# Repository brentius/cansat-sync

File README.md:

# CANSAT

Local working folder for the CANSAT project, organised using ATLAS as the reference.

The current mission uses a Raspberry Pi Zero 2 W and STM32F405 to combine primary temperature/pressure telemetry with terrain-relative navigation during passive parachute descent and image-derived wind profiling. The selected hardware is defined by the [flight computer BOM](wiki/flight_computer_bom.md) and summarised in the [current design baseline](wiki/design_baseline.md).

The [all-board BOM summary](wiki/board_bom_summary.md) allocates the selected POWER, MAIN and RF boards, plus Pi, camera and shared offboard purchases. POWER contains supply electronics; MAIN contains the MCU, sensors and interfaces. The previous KiCad projects were cleared on 29 October 2026 to restart PCB design; the BOM and design notes remain reference material, and descriptions of the previous CAD are historical.

## File structure

```text
cansat/
├── pcb/                   Schematics, PCB layouts and parts libraries
├── code/                  Onboard software, ground software and data processing
├── cad/                   Mechanical designs and assembly models
├── sim/                   Simulations, analysis scripts and results
├── wiki/                  Mission proposals, documentation and reference notes
├── BOTS/
│   ├── AGENTS/            Local agent instructions
│   └── PLANS/             Architecture, plans, decisions and project status
├── README.md
├── LICENSE-HARDWARE
├── LICENSE-SOFTWARE
└── .gitignore
```

## Onboard software

The [flight software implementation report](wiki/flight_software.md) describes the
STM32 firmware, Pi service/navigation, design choices, verification and hardware
next steps. Sources are in `code/firmware/stm32`, `code/cansat`, `code/piapp` and
`code/deploy/pi`. Reproduce the combined host/cross-build gate with
`.venv/Scripts/python.exe code/tools/verify_flight.py`.

## Mission documentation

The [mission proposal](wiki/trn_secondary_mission_proposal.md) was rewritten on 13 October 2026 around the current BOM, reference interfaces and newer feasibility studies. It includes both mission software paths and distinguishes selected hardware, candidate code, targets and verified evidence. The [27 September proposal](wiki/history/trn_secondary_mission_proposal_2026-09-27.md) is retained as a historical source snapshot; it is not the current design. The original ChatGPT project source remains separate.

The standalone [mathematical derivations and verification document](wiki/cansat_mathematics.tex) covers the proposal's mathematics index, corrected assumptions, worked examples and synthetic experiments. It needs no external source files to compile and compiled successfully with the built-in editor on 13 October 2026. Its historical example inputs are preserved alongside current BOM context. The supplied 52-page PDF remains a separate historical attachment that has been audited.

The [simulation and feasibility audit](wiki/mathematics_simulation_audit.md) maps all 249 numbered PDF equations to checks and restrictions, with 76 tests reported passing in the retained audit, rendered-image experiments, navigation and atmospheric uncertainty ensembles, and processing budgets. It records a transfer-function typo and a corrected NCC memory problem. Numerical consistency is established under the tested assumptions; flight performance and current Pi Zero 2 W throughput remain unverified. Historical H618/OV9281 sizing is explicitly separated from the current baseline. Supporting code and retained results are in `sim/maths/`; project state is recorded in `BOTS/PLANS/`.

A [second review of that PDF](wiki/cansat_maths_pdf_review.md) on 13 October re-derived all 249 equations and recomputed the stated numbers: the mathematics is correct apart from one known typo and a few small slips. It also lists where the PDF's inputs and conclusions no longer match the current baseline, which of its corrections the live proposal has not yet taken up, and where the flight code departs from it. No simulation was rerun and no source was changed.

The [closed-loop navigation simulation](wiki/navigation_closed_loop_simulation.md) runs a candidate flight navigation filter (`code/cansat/eskf.py`, initialised from `code/cansat/firstfix.py` pose outputs) against a simulated parachute descent in `sim/nav/`: 109 scenarios of 160 descents each, an image-in-the-loop cross-check, a matcher-tolerance study and a canopy swing and glide study. In simulation the September proposal's plain filter loses lock under realistic errors, while the current proposal uses the hardened 17-error-state candidate, which holds about 0.6 m RMS relative to the simulated map. Canopy glide remains a major threat to wind retrieval. The acquisition-to-filter handoff is now implemented in `navigator.py`; the flight-software report covers its separate integrated evidence. All of it is synthetic: no real imagery, flight data or Pi timing yet. Inputs and their sources are in [navigation parameter sources](wiki/navigation_parameter_sources.md).

The [fine landmark tracking implementation and study](wiki/fine_landmark_tracking.md) adds the missing local image matcher in `code/cansat/fine.py`: prepared map templates, predicted-pose rectification, bounded spatial selection, ambiguity rejection and original-pixel measurements for the existing filter. `sim/nav/run_fine_mc.py` tests repeated image-to-filter corrections on procedural farmland with paired no-image controls and appearance/capture-limit stress cases. It is candidate software with synthetic verification; live acquisition/tracking orchestration is now implemented; real-image/Pi validation remains open.

The [end-to-end wind and landing study](wiki/wind_retrieval_end_to_end.md) carries that filter's output through to the mission's science products: a wind retrieval (`code/cansat/windprofile.py`) and a candidate landing predictor for the Pi Zero 2 W (`code/cansat/landing.py`), scored in `sim/nav/run_wind_mc.py` over five canopy behaviours. In simulation the simple drag-model retrieval meets its 0.5 m/s absolute-error target under a stable canopy and one with a 5 degree trim, and fails with a 12 or 25 degree trim or heavy swing, while the S1 comparison of image and GPS winds passes in every case. The current proposal therefore defines S1 as method agreement and treats absolute wind recovery and lateral-force correction as calibration-dependent. One descent's winds between 80 m and 300 m do not determine roughness length without the ground anemometer. All of it is synthetic and nothing has run on the flight hardware. Literature inputs and their evidence quality are in [wind science parameter sources](wiki/wind_science_parameter_sources.md).

The [first-fix study](wiki/acquisition_first_fix.md) covers the step before that filter can start: finding where the can is, and which way it faces, from one image with the heading unknown. `code/cansat/coarse.py` is flight code for the Pi Zero 2 W that does it in four stages and refuses instead of guessing; `sim/nav/run_acquisition_mc.py` scores it on procedural farmland (`sim/nav/farmland.py`) with rendered images and simulated descents. In simulation it gives a fix from about nine images in ten on well-hedged terrain and about four in ten on large fields, where it is also wrong more often, so the result depends on the launch site and needs real imagery of it. An independent review found seven defects, all fixed. All of it is synthetic and nothing has run on the Pi.

The [STM32-to-Pi link protocol](wiki/stm32_pi_link_protocol.md) defines the serial link between the two processors, which did not exist before: framing, twelve messages, the time base, and how camera frames get their timestamps. `code/cansat/link.py` is the Pi's end and the reference the STM32 firmware has to match, with test vectors in `code/tests/link_vectors.json`. It was checked in closed loop against the navigation Monte Carlo (`sim/nav/run_link_mc.py`). The C firmware and Pi service now exist; host/cross-build verification is recorded in the flight-software report. Nothing has been executed on either physical processor.

The [mass, power and descent budget](wiki/mass_power_budget.md) replaces the 1 October sizing, which was for hardware the project no longer uses. For the current design it expects about 335 g against the 350 g limit with a 6 to 15 % chance of exceeding it, a wide margin on three hours of power if the Pi idles while waiting, and a design descent rate too close to the 10 m/s floor. Nothing in it has been weighed or metered. The model is `sim/systems/budget.py`.

The [PDR checklist](BOTS/PLANS/PDR_FULL_MARKS_CHECKLIST.md) maps the supplied 36-point rubric and all available requirements. Those requirements are still from 2025-26; current-season rules/dates need confirmation. Completed analysis is documented separately from open firmware, physical packaging, calibration, target compute, mass/cost and flight qualification.

## Licenses

Following ATLAS, hardware designs in `pcb/` and `cad/`, and hardware circuit netlists in `sim/`, use CERN-OHL-S-2.0; software in `code/` and simulation scripts in `sim/` use GPL-3.0-only. See `LICENSE-HARDWARE` and `LICENSE-SOFTWARE`.

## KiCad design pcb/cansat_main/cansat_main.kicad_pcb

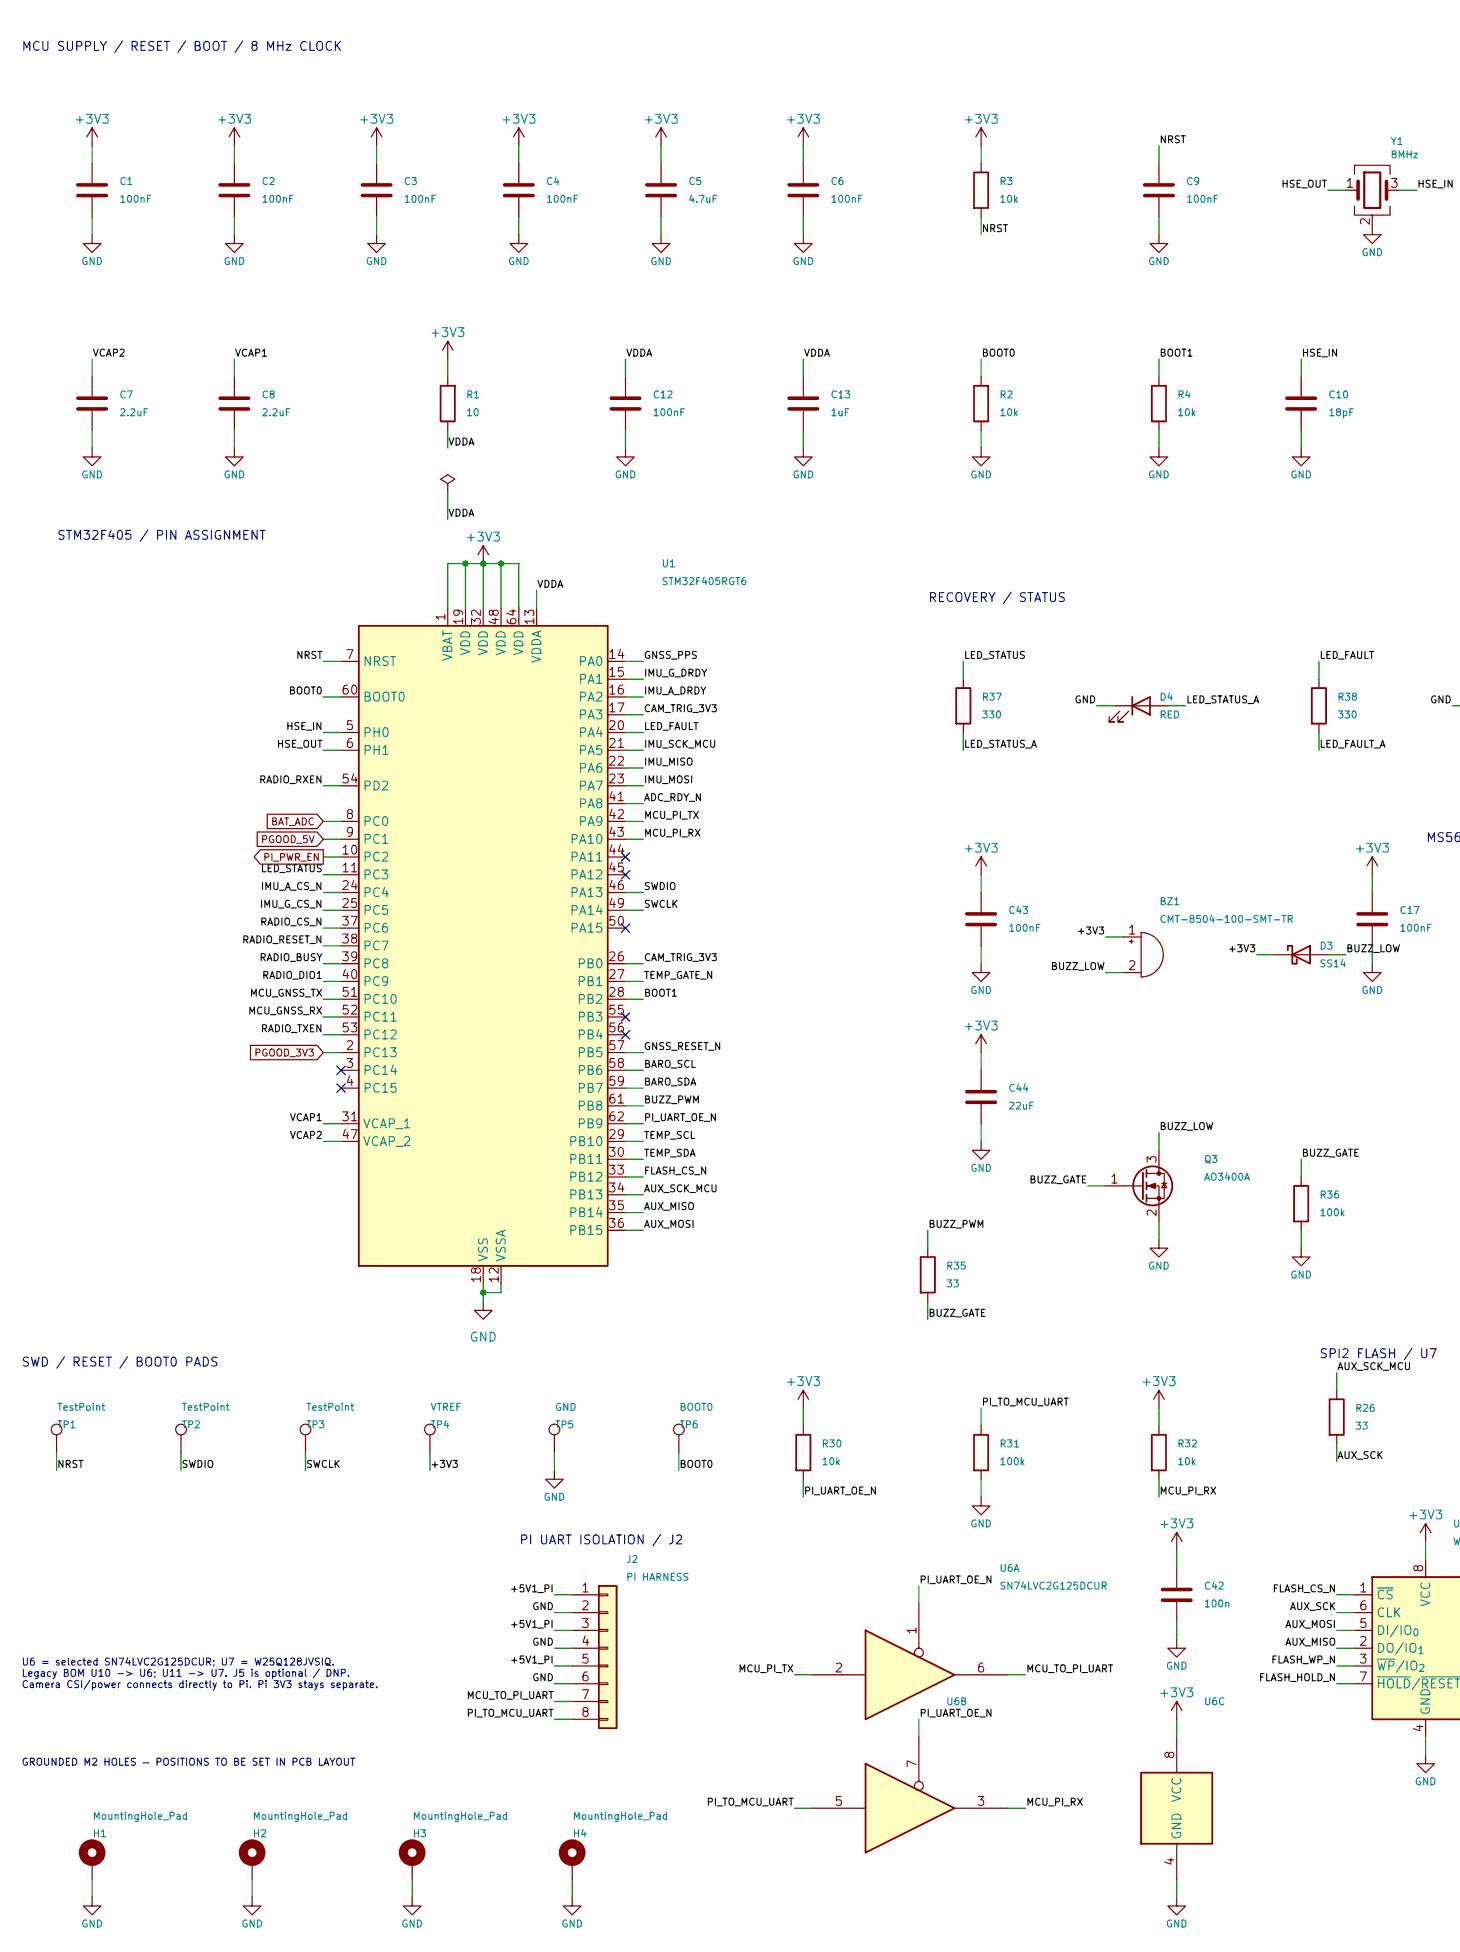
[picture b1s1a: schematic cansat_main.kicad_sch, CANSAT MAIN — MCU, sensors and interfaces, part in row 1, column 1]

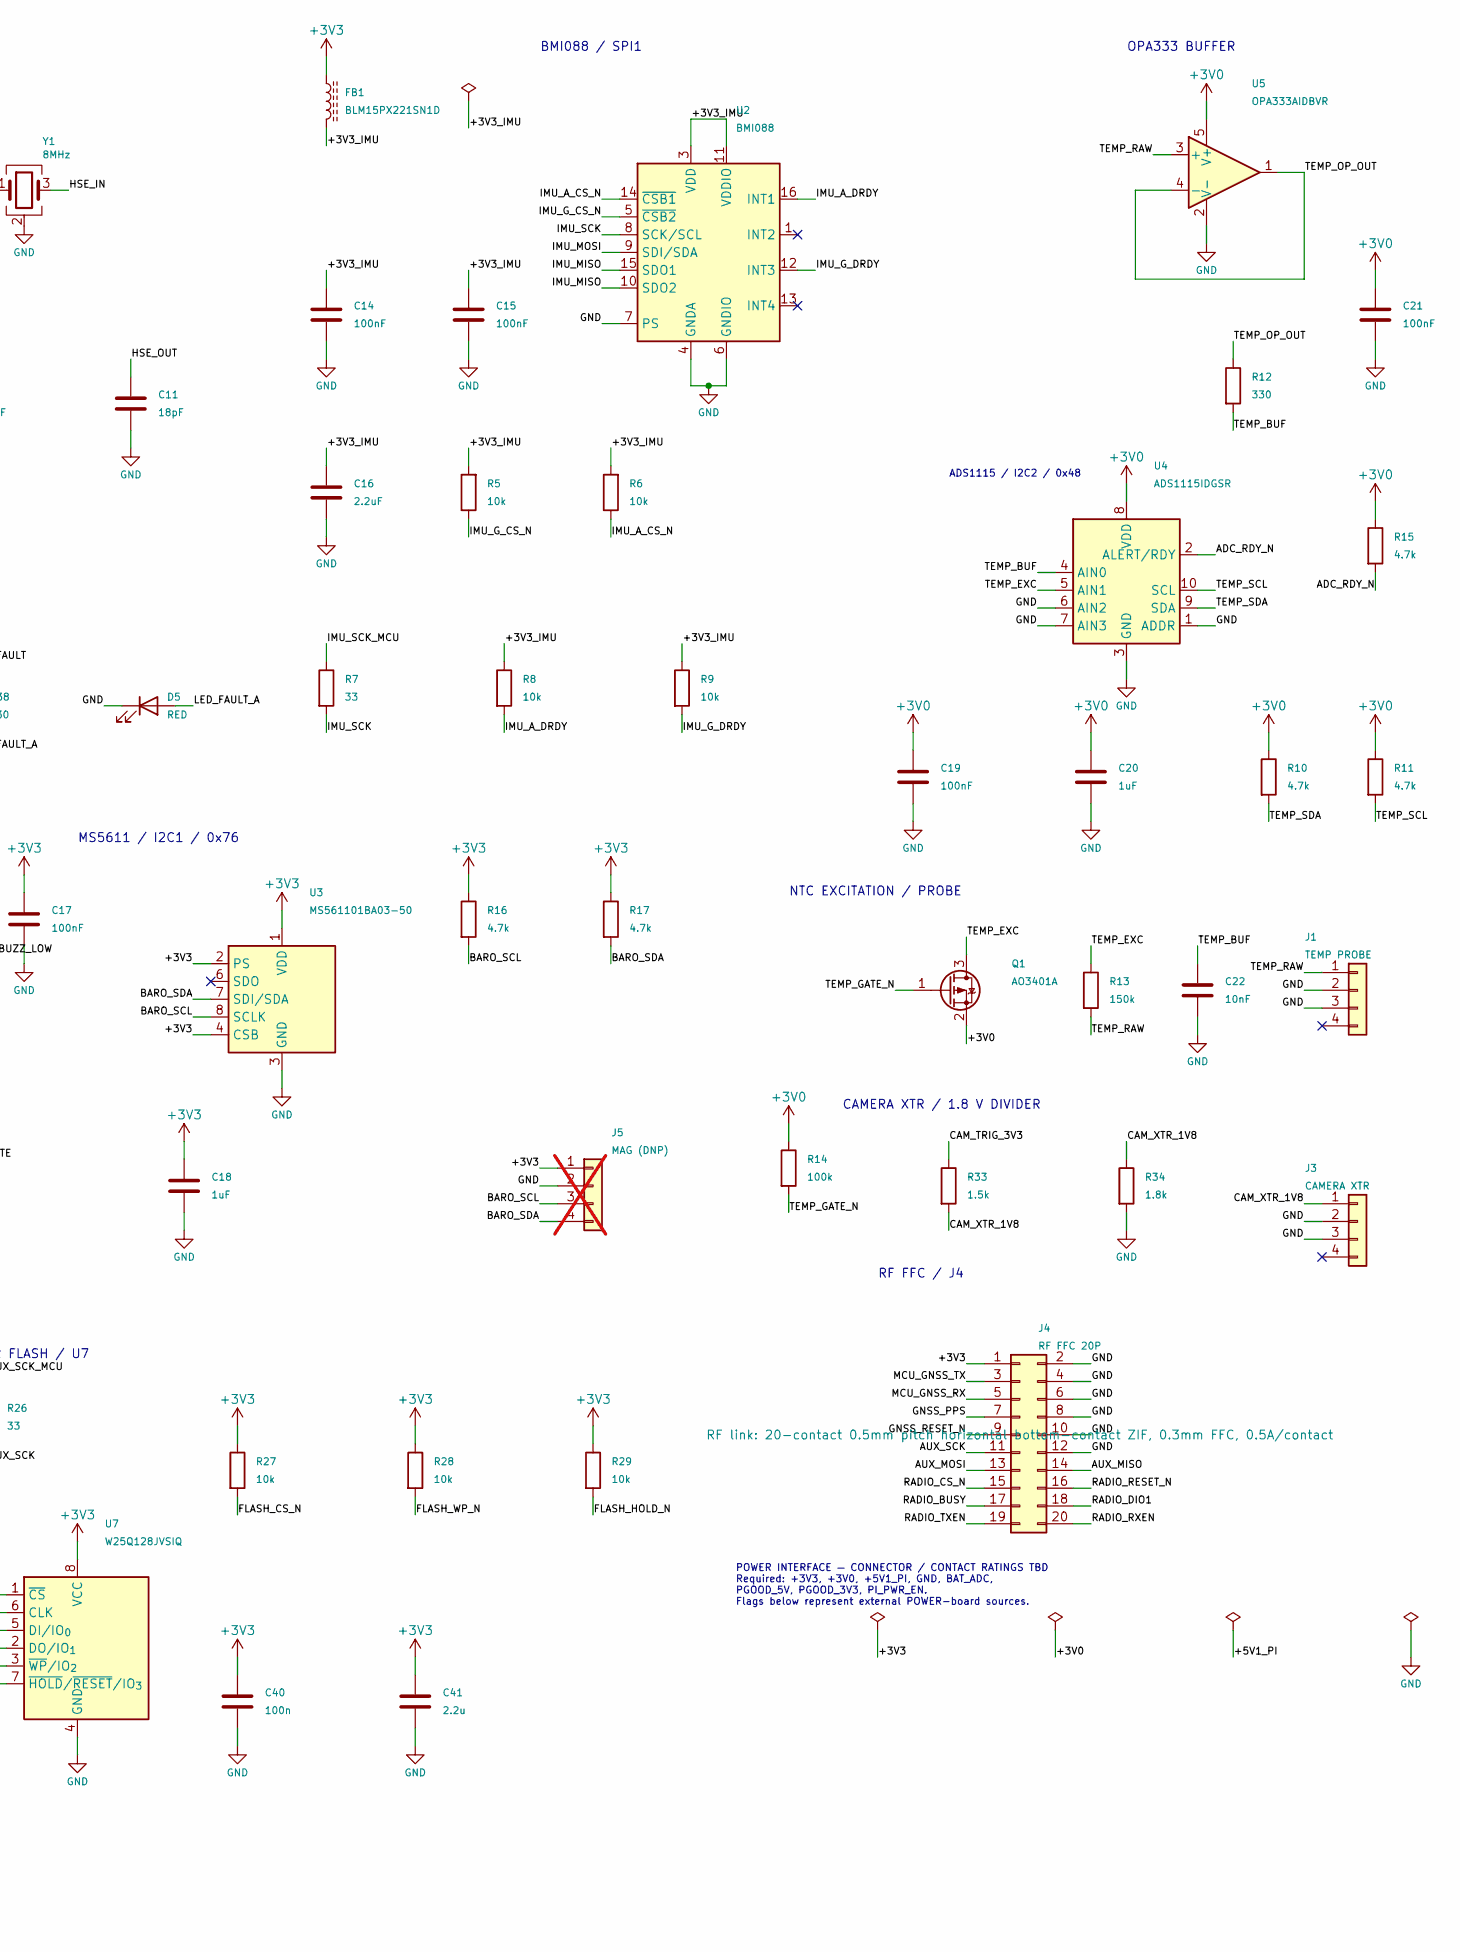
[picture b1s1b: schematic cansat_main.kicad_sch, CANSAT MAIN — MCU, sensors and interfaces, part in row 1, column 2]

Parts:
BZ1: CMT-8504-100-SMT-TR; MagneticBuzzer_CUI_CMT-8504-100-SMT; MPN CMT-8504-100-SMT-TR; JLCPCB C22359707
C1, C2, C3, C4, C6, C9, C12, C14, C15: 100nF; C_0402_1005Metric; MPN CL05B104KO5NNNC; LCSC C1525
C5: 4.7uF; C_0805_2012Metric; Voltage Rating 16V; Tolerance 10%; Manufacturer Part Number CL21A475KOFNNNE; JLCPCB Part # C1746
C7, C8: 2.2uF; C_0603_1608Metric; MPN CL10A225KP8NNNC; LCSC C1607
C10, C11: 18pF; C_0402_1005Metric; MPN CL05C180JB5NNNC; LCSC C307443
C13: 1uF; C_0402_1005Metric; MPN CL05A105KA5NQNC; LCSC C52923
C16: 2.2uF; C_0402_1005Metric; Manufacturer Part Number CL05A225KA5NUNC; JLCPCB Part # C307418
C17, C19, C21: 100nF; C_0402_1005Metric; Manufacturer Part Number CL05B104KO5NNNC; JLCPCB Part # C1525
C18, C20: 1uF; C_0402_1005Metric; Manufacturer Part Number CL05A105KA5NQNC; JLCPCB Part # C52923
C22: 10nF; C_0402_1005Metric; Manufacturer Part Number CL05B103KB5NNNC; JLCPCB Part # C15195
C40, C42: 100n; C_0402_1005Metric; MPN CL05B104KO5NNNC; JLCPCB C1525
C41: 2.2u; C_0402_1005Metric; MPN CL05A225KA5NUNC; JLCPCB C307418
C43: 100nF; C_0402_1005Metric; MPN CL05B104KO5NNNC; JLCPCB C1525
C44: 22uF; C_0805_2012Metric; MPN CL21A226MAYNNNE; JLCPCB C602037
D3: SS14; D_SMA; MPN SS14; JLCPCB C2480
D4, D5: RED; LED_0402_1005Metric; MPN 16-213SDRC/S530-A3/TR8; JLCPCB C71911
FB1: BLM15PX221SN1D; L_0402_1005Metric; Manufacturer Part Number BLM15PX221SN1D; JLCPCB Part # C160973
H1, H2, H3, H4: MountingHole_Pad; MountingHole_2.2mm_M2_DIN965_Pad
J1: TEMP PROBE; JST_GH_BM04B-GHS-TBT_1x04-1MP_P1.25mm_Vertical; MPN BM04B-GHS-TBT(LF)(SN); LCSC C161692
J2: PI HARNESS; JST_GH_BM08B-GHS-TBT_1x08-1MP_P1.25mm_Vertical; MPN BM08B-GHS-TBT(LF)(SN); JLCPCB C133062
J3: CAMERA XTR; JST_GH_BM04B-GHS-TBT_1x04-1MP_P1.25mm_Vertical; MPN BM04B-GHS-TBT(LF)(SN); JLCPCB C161692
J4: RF FFC 20P; Hirose_FH12-20S-0.5SH_1x20-1MP_P0.50mm_Horizontal; MPN FH12-20S-0.5SH(55); JLCPCB C596730
J5: MAG (DNP); JST_GH_BM04B-GHS-TBT_1x04-1MP_P1.25mm_Vertical; MPN BM04B-GHS-TBT(LF)(SN); JLCPCB C161692; not fitted
Q1: AO3401A; SOT-23; MPN AO3401A; LCSC C15127
Q3: AO3400A; SOT-23; MPN AO3400A; JLCPCB C20917
R1: 10; R_0402_1005Metric; MPN RC0402FR-0710RL; LCSC C138066
R2, R3, R4, R5, R6: 10k; R_0402_1005Metric; MPN RC0402FR-0710KL; LCSC C60490
R7: 33; R_0402_1005Metric; MPN RC0402FR-0733RL; LCSC C138002
R8, R9: 10k; R_0402_1005Metric; Manufacturer Part Number RC0402FR-0710KL; JLCPCB Part # C60490
R10, R11: 4.7k; R_0402_1005Metric; MPN RC0402FR-074K7L; LCSC C105871
R12: 330; R_0402_1005Metric; Manufacturer Part Number RC0402FR-07330RL; JLCPCB Part # C105875
R13: 150k; R_0402_1005Metric; Manufacturer Part Number RT0402BRD07150KL; JLCPCB Part # C852538
R14: 100k; R_0402_1005Metric; Manufacturer Part Number RC0402FR-07100KL; JLCPCB Part # C60491
R15, R16, R17: 4.7k; R_0402_1005Metric; Manufacturer Part Number RC0402FR-074K7L; JLCPCB Part # C105871
R26, R35: 33; R_0402_1005Metric; MPN RC0402FR-0733RL; JLCPCB C138002
R27, R28, R29, R30, R32: 10k; R_0402_1005Metric; MPN RC0402FR-0710KL; JLCPCB C60490
R31, R36: 100k; R_0402_1005Metric; MPN RC0402FR-07100KL; JLCPCB C60491
R33: 1.5k; R_0402_1005Metric; MPN RC0402FR-071K5L; JLCPCB C114759
R34: 1.8k; R_0402_1005Metric; MPN RC0402FR-071K8L; JLCPCB C163481
R37, R38: 330; R_0402_1005Metric; MPN RC0402FR-07330RL; JLCPCB C105875
TP1, TP2, TP3: TestPoint; TestPoint_Pad_D1.0mm
TP4: VTREF; TestPoint_Pad_D1.0mm
TP5: GND; TestPoint_Pad_D1.0mm
TP6: BOOT0; TestPoint_Pad_D1.0mm
U1: STM32F405RGT6; LQFP-64_10x10mm_P0.5mm_CoreSilk; MPN STM32F405RGT6; LCSC C15742
U2: BMI088; Bosch_LGA-16_4.5x3mm_P0.5mm_LayoutBorder7x1y_ClockwisePinNu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; MPN BMI088; LCSC C194919
U3: MS561101BA03-50; LGA-8_3x5mm_P1.25mm; MPN MS561101BA03-50; LCSC C15639
U4: ADS1115IDGSR; TSSOP-10_3x3mm_P0.5mm; MPN ADS1115IDGSR; LCSC C37593
U5: OPA333AIDBVR; SOT-23-5; Manufacturer Part Number OPA333AIDBVR; JLCPCB Part # C30878
U6: SN74LVC2G125DCUR; VSSOP-8_2.3x2mm_P0.5mm; MPN SN74LVC2G125DCUR; JLCPCB C21404
U7: W25Q128JVSIQ; SOIC-8_5.3x5.3mm_P1.27mm; MPN W25Q128JVSIQ; LCSC C97521
Y1: 8MHz; Crystal_SMD_3225-4Pin_3.2x2.5mm; Manufacturer Part Number X32258MOB4SI; JLCPCB Part # C2682775

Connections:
+3V0: C19.1, C20.1, C21.1, Q1.2 (S), R10.1, R11.1, R14.1, R15.1, U4.8 (VDD), U5.5 (V+)
+3V3: BZ1.1 (+), C1.1, C2.1, C3.1, C4.1, C5.1, C6.2, C17.1, C18.1, C40.1, C41.1, C42.1, C43.1, C44.1, D3.1 (K), FB1.1, J4.1, J5.1, R1.2, R3.1, R16.1, R17.1, R27.1, R28.1, R29.1, R30.1, R32.1, TP4.1 (1_1), U1.1 (VBAT), U1.19 (VDD), U1.32 (VDD), U1.48 (VDD), U1.64 (VDD), U3.1 (VDD), U3.2 (PS), U3.4 (CSB), U3.5 (CSB), U6.8 (VCC), U7.8 (VCC)
/+3V3_IMU: C14.1, C15.1, C16.1, FB1.2, R5.2, R6.2, R8.1, R9.1, U2.3 (VDD), U2.11 (VDDIO)
/+5V1_PI: J2.1, J2.3, J2.5
/ADC_RDY_N: R15.2, U1.41 (PA8), U4.2 (ALERT/RDY)
/AUX_MISO: J4.14, U1.35 (PB14), U7.2 (DO/IO_{1})
/AUX_MOSI: J4.13, U1.36 (PB15), U7.5 (DI/IO_{0})
/AUX_SCK: J4.11, R26.2, U7.6 (CLK)
/AUX_SCK_MCU: R26.1, U1.34 (PB13)
/BARO_SCL: J5.3, R16.2, U1.58 (PB6), U3.8 (SCLK)
/BARO_SDA: J5.4, R17.2, U1.59 (PB7), U3.7 (SDI/SDA)
/BOOT0: R2.2, TP6.1 (1_1), U1.60 (BOOT0)
/BOOT1: R4.1, U1.28 (PB2)
/BUZZ_GATE: Q3.1 (G), R35.2, R36.1
/BUZZ_LOW: BZ1.2 (-), D3.2 (A), Q3.3 (D)
/BUZZ_PWM: R35.1, U1.61 (PB8)
/CAM_TRIG_3V3: R33.1, U1.17 (PA3), U1.26 (PB0)
/CAM_XTR_1V8: J3.1, R33.2, R34.1
/FLASH_CS_N: R27.2, U1.33 (PB12), U7.1 (~CS)
/FLASH_HOLD_N: R29.2, U7.7 (~HOLD/~RESET/IO_{3})
/FLASH_WP_N: R28.2, U7.3 (~WP/IO_{2})
/GNSS_PPS: J4.7, U1.14 (PA0)
/GNSS_RESET_N: J4.9, U1.57 (PB5)
/HSE_IN: C10.1, U1.5 (PH0), Y1.3
/HSE_OUT: C11.1, U1.6 (PH1), Y1.1
/IMU_A_CS_N: R6.1, U1.24 (PC4), U2.14 (~CSB1)
/IMU_A_DRDY: R8.2, U1.16 (PA2), U2.16 (INT1)
/IMU_G_CS_N: R5.1, U1.25 (PC5), U2.5 (~CSB2)
/IMU_G_DRDY: R9.2, U1.15 (PA1), U2.12 (INT3)
/IMU_MISO: U1.22 (PA6), U2.10 (SDO2), U2.15 (SDO1)
/IMU_MOSI: U1.23 (PA7), U2.9 (SDI/SDA)
/IMU_SCK: R7.2, U2.8 (SCK/SCL)
/IMU_SCK_MCU: R7.1, U1.21 (PA5)
/LED_FAULT: R38.1, U1.20 (PA4)
/LED_FAULT_A: D5.2 (A), R38.2
/LED_STATUS: R37.1, U1.11 (PC3)
/LED_STATUS_A: D4.2 (A), R37.2
/MCU_GNSS_RX: J4.5, U1.52 (PC11)
/MCU_GNSS_TX: J4.3, U1.51 (PC10)
/MCU_PI_RX: R32.2, U1.43 (PA10), U6.3
/MCU_PI_TX: U1.42 (PA9), U6.2
/MCU_TO_PI_UART: J2.7, U6.6
/NRST: C9.1, R3.2, TP1.1 (1_1), U1.7 (NRST)
/PI_TO_MCU_UART: J2.8, R31.1, U6.5
/PI_UART_OE_N: R30.2, U1.62 (PB9), U6.1, U6.7
/RADIO_BUSY: J4.17, U1.39 (PC8)
/RADIO_CS_N: J4.15, U1.37 (PC6)
/RADIO_DIO1: J4.18, U1.40 (PC9)
/RADIO_RESET_N: J4.16, U1.38 (PC7)
/RADIO_RXEN: J4.20, U1.54 (PD2)
/RADIO_TXEN: J4.19, U1.53 (PC12)
/SWCLK: TP3.1 (1_1), U1.49 (PA14)
/SWDIO: TP2.1 (1_1), U1.46 (PA13)
/TEMP_BUF: C22.1, R12.2, U4.4 (AIN0)
/TEMP_EXC: Q1.3 (D), R13.1, U4.5 (AIN1)
/TEMP_GATE_N: Q1.1 (G), R14.2, U1.27 (PB1)
/TEMP_OP_OUT: R12.1, U5.1, U5.4 (-)
/TEMP_RAW: J1.1, R13.2, U5.3 (+)
/TEMP_SCL: R11.2, U1.29 (PB10), U4.10 (SCL)
/TEMP_SDA: R10.2, U1.30 (PB11), U4.9 (SDA)
/VCAP1: C8.1, U1.31 (VCAP_1)
/VCAP2: C7.1, U1.47 (VCAP_2)
/VDDA: C12.2, C13.2, R1.1, U1.13 (VDDA)
BAT_ADC: U1.8 (PC0)
GND: C1.2, C2.2, C3.2, C4.2, C5.2, C6.1, C7.2, C8.2, C9.2, C10.2, C11.2, C12.1, C13.1, C14.2, C15.2, C16.2, C17.2, C18.2, C19.2, C20.2, C21.2, C22.2, C40.2, C41.2, C42.2, C43.2, C44.2, D4.1 (K), D5.1 (K), H1.1 (1_1), H2.1 (1_1), H3.1 (1_1), H4.1 (1_1), J1.2, J1.3, J2.2, J2.4, J2.6, J3.2, J3.3, J4.2, J4.4, J4.6, J4.8, J4.10, J4.12, J5.2, Q3.2 (S), R2.1, R4.2, R31.2, R34.2, R36.2, TP5.1 (1_1), U1.12 (VSSA), U1.18 (VSS), U1.63 (VSS), U2.2 (GNDA), U2.4 (GNDA), U2.6 (GNDIO), U2.7 (PS), U3.3 (GND), U4.1 (ADDR), U4.3 (GND), U4.6 (AIN2), U4.7 (AIN3), U5.2 (V-), U6.4 (GND), U7.4 (GND), Y1.2 (G), Y1.4 (G)
PGOOD_3V3: U1.2 (PC13)
PGOOD_5V: U1.9 (PC1)
PI_PWR_EN: U1.10 (PC2)

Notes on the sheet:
STM32F405 / PIN ASSIGNMENT
POWER INTERFACE — CONNECTOR / CONTACT RATINGS TBD Required: +3V3, +3V0, +5V1_PI, GND, BAT_ADC, PGOOD_5V, PGOOD_3V3, PI_PWR_EN. Flags below represent external POWER-board sources.
U6 = selected SN74LVC2G125DCUR; U7 = W25Q128JVSIQ. Legacy BOM U10 -> U6; U11 -> U7. J5 is optional / DNP. Camera CSI/power connects directly to Pi. Pi 3V3 stays separate.
SPI2 FLASH / U7
MS5611 / I2C1 / 0x76
CAMERA XTR / 1.8 V DIVIDER
GROUNDED M2 HOLES — POSITIONS TO BE SET IN PCB LAYOUT
OPA333 BUFFER
PI UART ISOLATION / J2
RF FFC / J4
RECOVERY / STATUS
BMI088 / SPI1
NTC EXCITATION / PROBE
MCU SUPPLY / RESET / BOOT / 8 MHz CLOCK
ADS1115 / I2C2 / 0x48
SWD / RESET / BOOT0 PADS

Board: 4 copper layers, 87 parts (0 on the bottom side), 64 nets, no tracks yet.
